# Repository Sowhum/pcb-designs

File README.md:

# pcb-designs
Custom PCB designs

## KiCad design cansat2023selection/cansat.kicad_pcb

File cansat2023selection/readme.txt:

ESP 32 WROOM 32E is powered using a 3.3V coin cell wired through a SPST switch 

The 32E has no dedicated pins , here i used GPIO pins for most of the connections including SDO,SDI,SCK and powering the components with 3.3V

LCD connection was done by following the provided tutorial and comparing pinouts of  ESP 32 in the turorial with the 32E

BMP280 connection was done by following the example given in it's datasheet for i2C

Due to limitations of size and the LCD taking most of the space in front, all other components except the switch have been placed on the back

Two of these are surface mounts(the ESP32 and the BMP280) so vias are used for most of their connections

The through hole components under the LCD have enough clearance

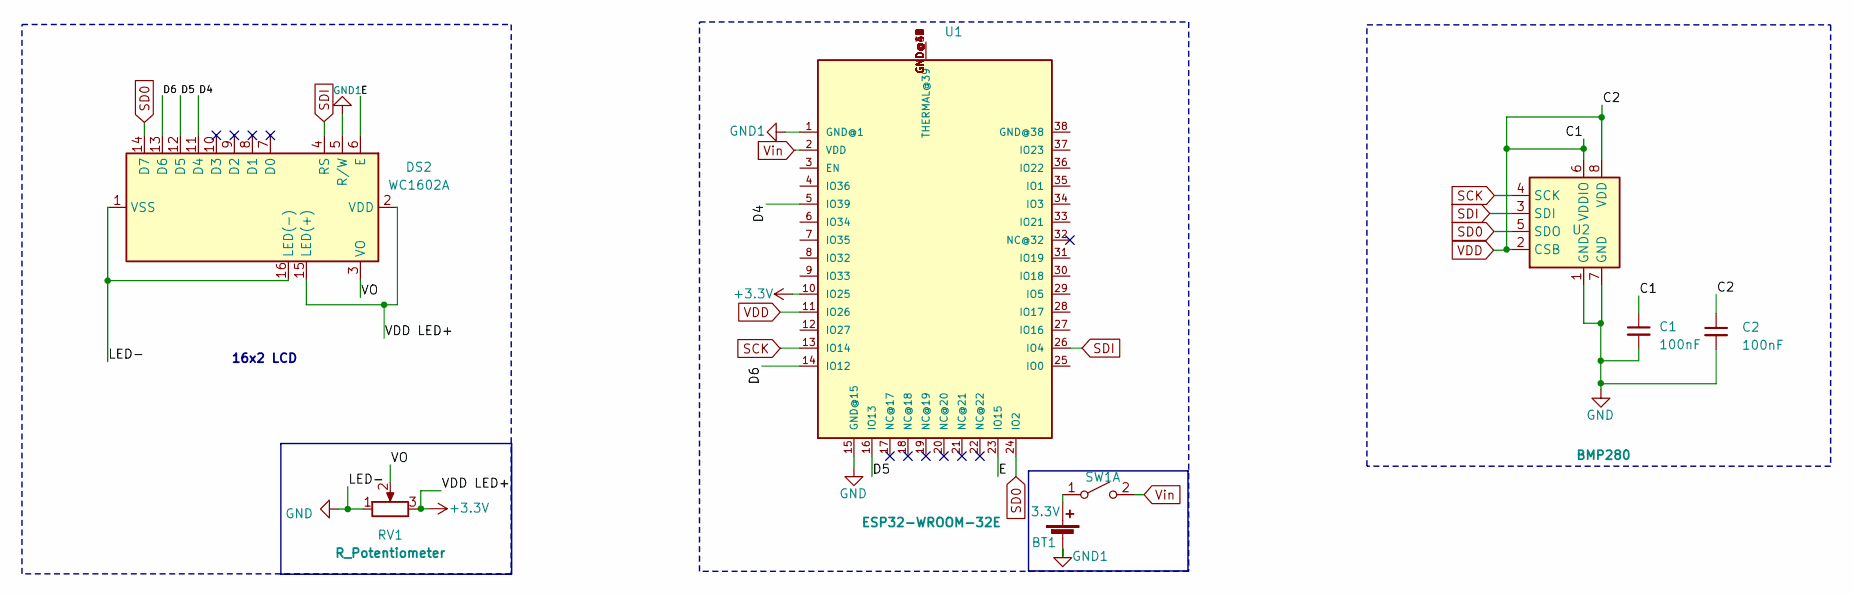
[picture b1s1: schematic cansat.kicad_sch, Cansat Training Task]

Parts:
BT1: 3.3V; BatteryHolder_Keystone_103_1x20mm
C1, C2: 100nF; C_Axial_L3.8mm_D2.6mm_P7.50mm_Horizontal
DS2: WC1602A
RV1: R_Potentiometer; Potentiometer_Bourns_3266P_Horizontal
SW1: SW_DIP_SPSTx01_Slide_9.78x4.72mm_W7.62mm_P2.54mm
U1: ESP32-WROOM-32E
U2: BMP280; Bosch_LGA-8_2x2.5mm_P0.65mm_ClockwisePinNumbering

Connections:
+3.3V: DS2.2 (VDD), DS2.15 (LED(+)), RV1.3, U1.10 (IO25)
/D4: DS2.11 (D4), U1.5 (IO39)
/D5: DS2.12 (D5), U1.16 (IO13)
/D6: DS2.13 (D6), U1.14 (IO12)
/E: DS2.6 (E), U1.23 (IO15)
/VO: DS2.3 (VO), RV1.2
GND: C1.2, C2.2, DS2.1 (VSS), DS2.16 (LED(-)), RV1.1, U1.15 (GND@15), U2.1 (GND), U2.7 (GND)
GND1: BT1.2 (-), DS2.5 (R/W), U1.1 (GND@1)
unnamed: BT1.1 (+), SW1.1 (A)
unnamed: U1.GND@39 (THERMAL@39), U1.GND@40 (THERMAL@39), U1.GND@41 (THERMAL@39), U1.GND@42 (THERMAL@39), U1.GND@43 (THERMAL@39), U1.GND@44 (THERMAL@39), U1.GND@45 (THERMAL@39), U1.GND@46 (THERMAL@39), U1.GND@47 (THERMAL@39)
SCK: U1.13 (IO14), U2.4 (SCK)
SD0: DS2.14 (D7), U1.24 (IO2), U2.5 (SDO)
SDI: DS2.4 (RS), U1.26 (IO4), U2.3 (SDI)
VDD: C1.1, C2.1, U1.11 (IO26), U2.2 (CSB), U2.6 (VDDIO), U2.8 (VDD)
Vin: SW1.2 (B), U1.2 (VDD)

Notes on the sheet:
16x2 LCD

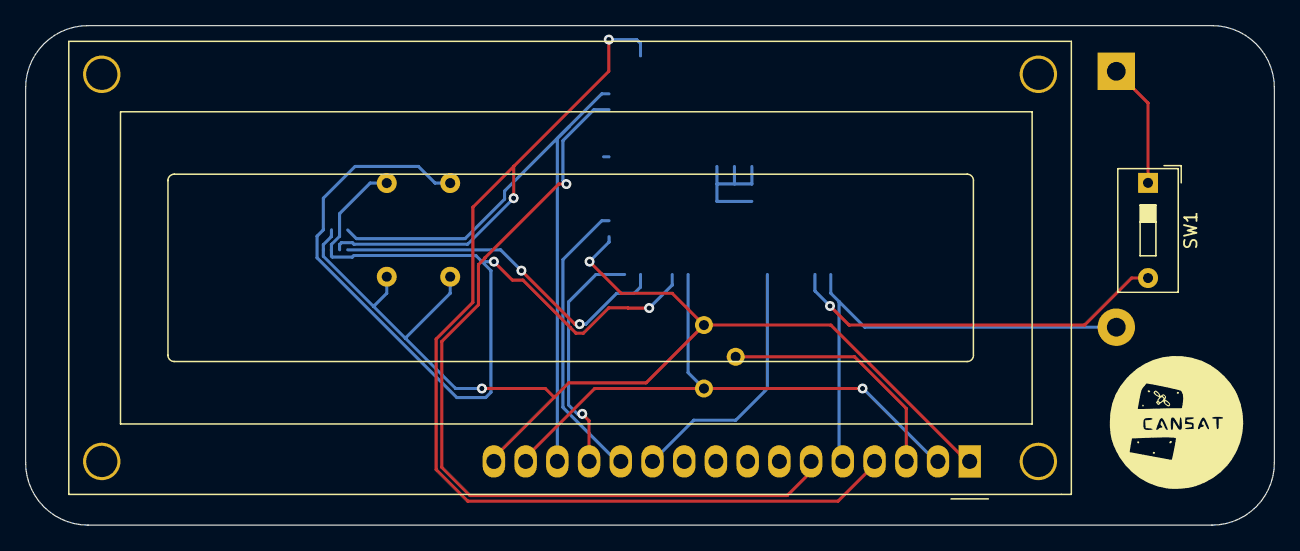
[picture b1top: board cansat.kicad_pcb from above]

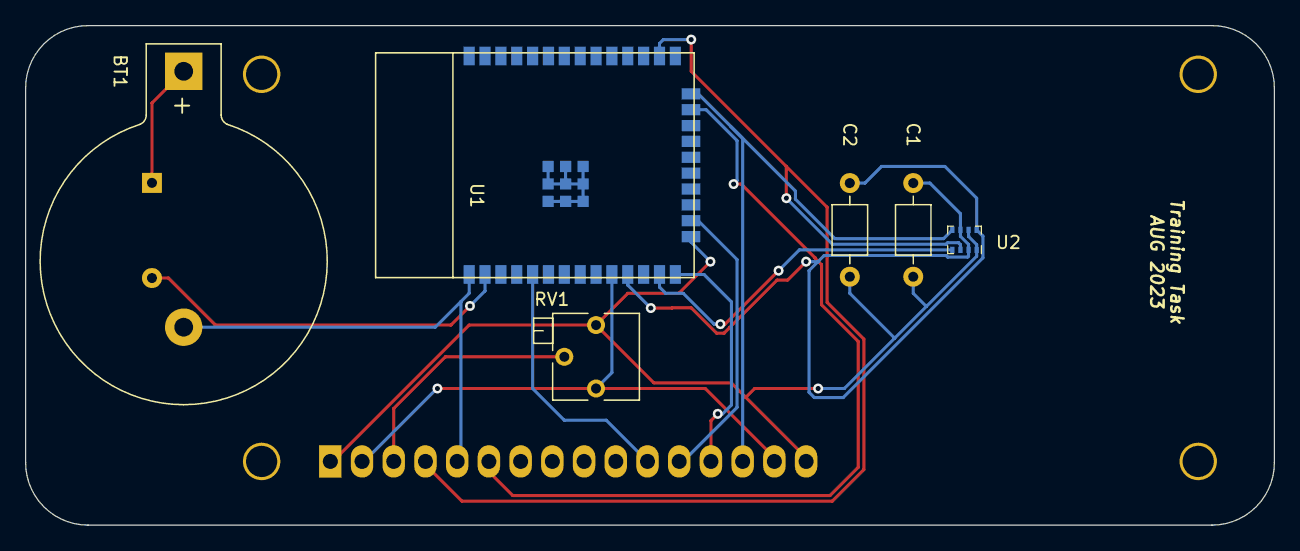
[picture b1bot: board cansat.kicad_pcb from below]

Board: 2 copper layers, 100.0 x 40.0 mm, 8 parts (6 on the bottom side), 15 nets.

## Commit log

2024-01-23 Add files via upload
    Design for an entry in a CanSat student group. All done in KiCAD
2024-01-23 Add files via upload
    PCB design for a Power regulator, made completely in Altium
